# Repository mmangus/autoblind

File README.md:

# Autoblind

## Schematic
[PDF](eda/Autoblind.pdf)

[KiCad file](eda/Autoblind.sch)

## Renders

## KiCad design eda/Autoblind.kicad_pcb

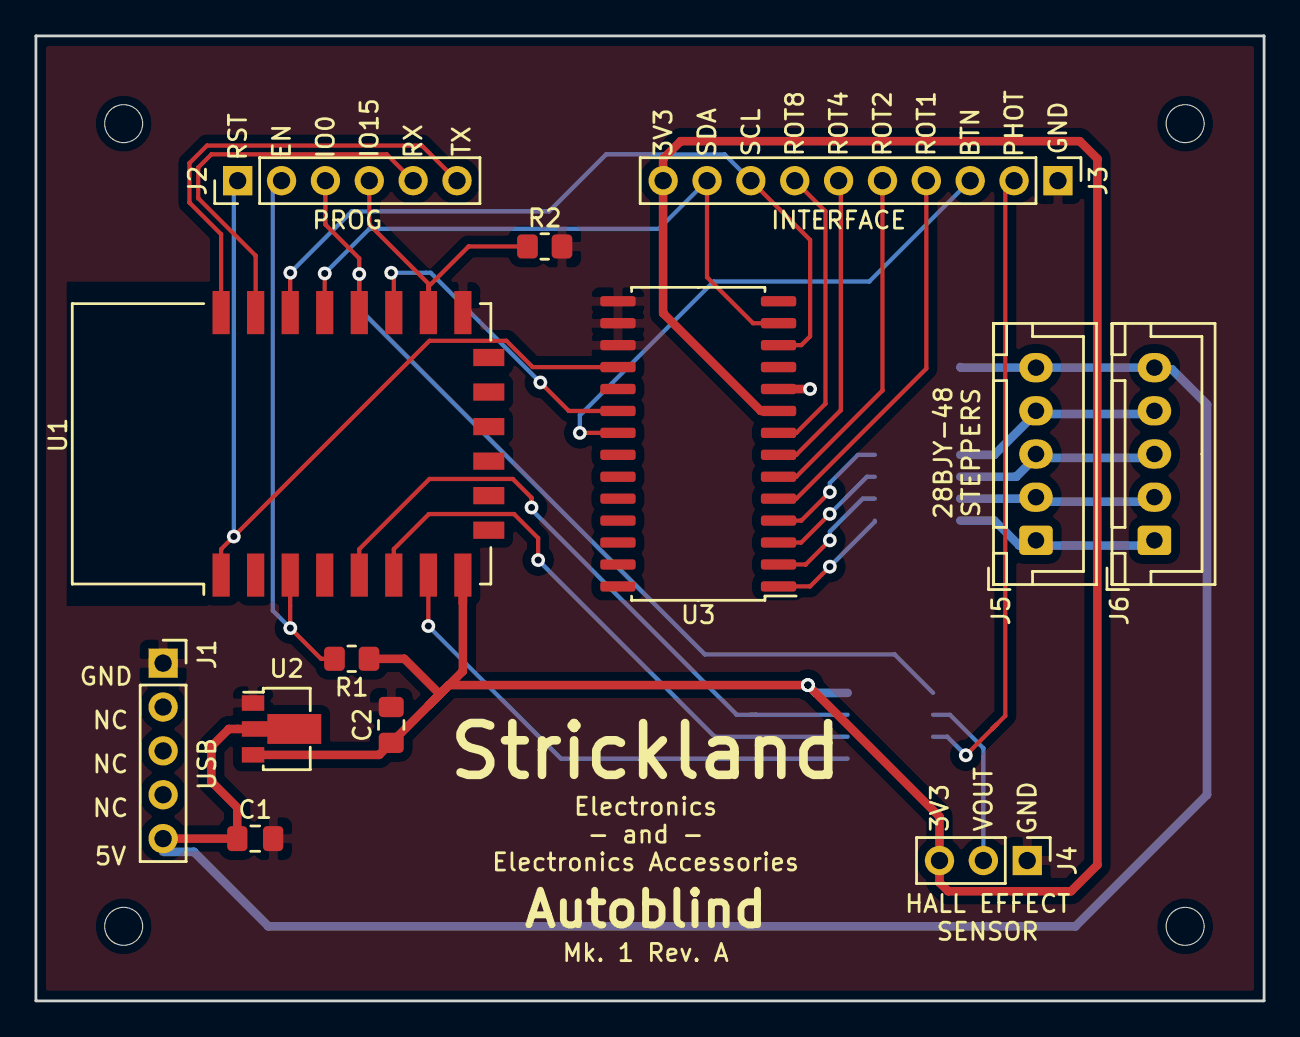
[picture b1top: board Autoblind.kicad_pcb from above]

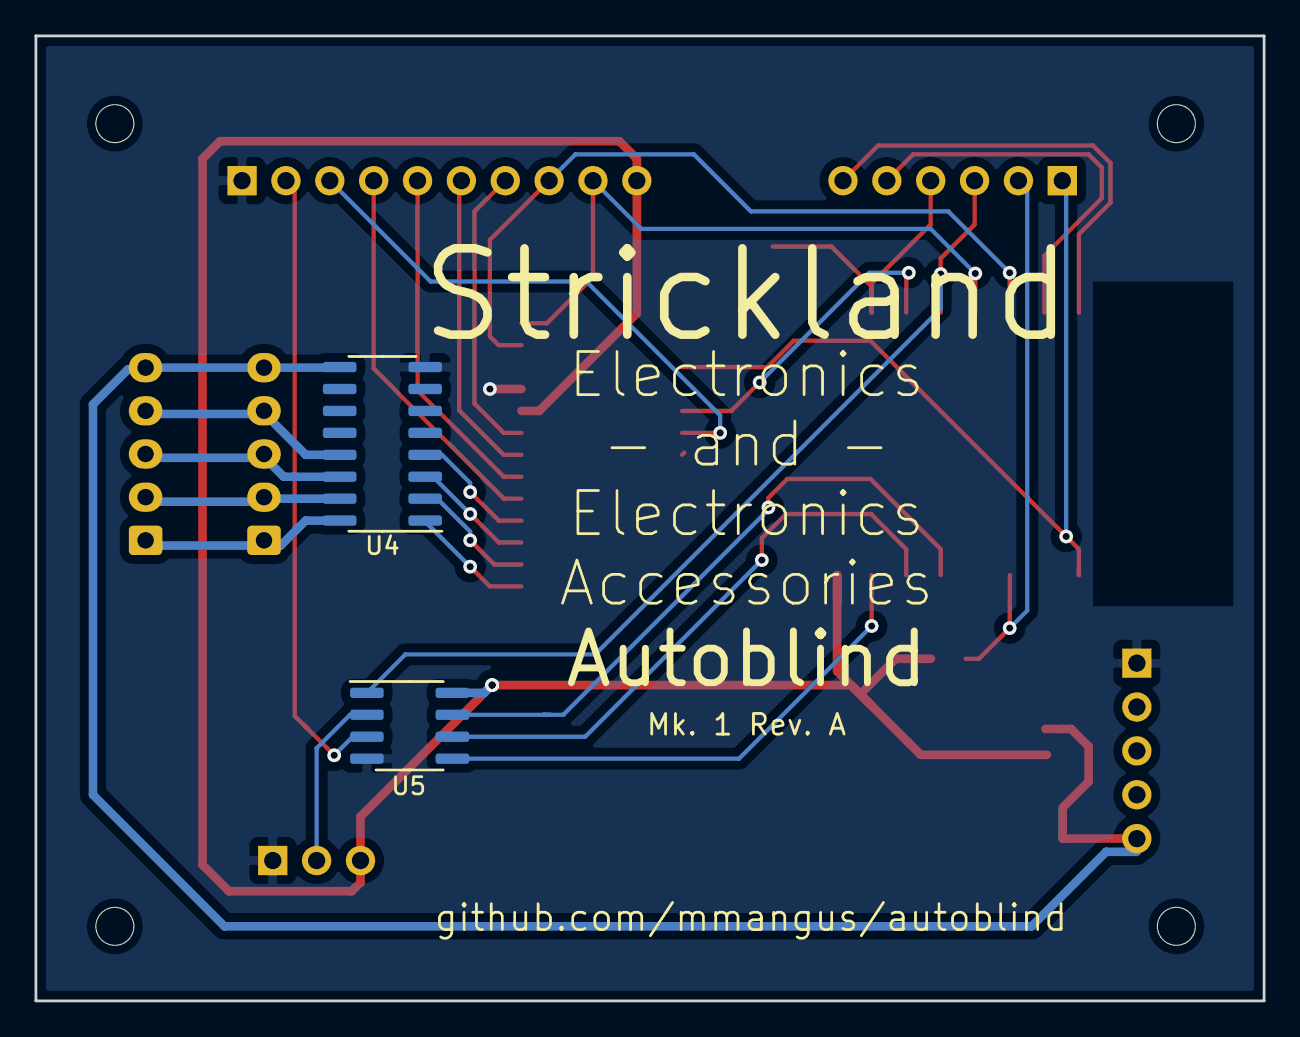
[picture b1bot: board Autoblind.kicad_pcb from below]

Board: 2 copper layers, 71.1 x 55.9 mm, 19 parts (2 on the bottom side), 30 nets.

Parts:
 : MountingHole_2.2mm_M2
 #2,  #3,  #4: MountingHole_2.2mm_M2
C1, C2: 2.2uF; C_0805_2012Metric_Pad1.18x1.45mm_HandSolder
J1: Conn_01x05; PinSocket_1x05_P2.54mm_Vertical
J2: Conn_01x06; PinHeader_1x06_P2.54mm_Vertical
J3: Conn_01x10; PinHeader_1x10_P2.54mm_Vertical
J4: Conn_01x03; PinHeader_1x03_P2.54mm_Vertical
J5, J6: Conn_01x05; JST_XH_B5B-XH-A_1x05_P2.50mm_Vertical
R1: 1K; R_0805_2012Metric_Pad1.20x1.40mm_HandSolder
R2: 470R; R_0805_2012Metric_Pad1.20x1.40mm_HandSolder
U1: ESP-12E
U2: HT7833; SOT-89-3
U3: MCP23017_SO; SOIC-28W_7.5x17.9mm_P1.27mm
U4: ULN2003; SOIC-16_3.9x9.9mm_P1.27mm
U5: MCP3002; SOIC-8_3.9x4.9mm_P1.27mm

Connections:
+3V3: C2.1, J3.10, J4.3, R1.1, U1.8, U2.3, U3.9, U5.8
+5V: C1.1, J1.5, J5.5, J6.5, U2.2, U4.9
/BLUE: J5.1, J6.1, U4.16
/BOOT: J2.4, R2.1, U1.16
/BTN: J3.3, U3.21
/COIL1: U3.1, U4.1
/COIL2: U3.2, U4.2
/COIL3: U3.3, U4.3
/COIL4: U3.4, U4.4
/CS: J2.3, U1.18, U5.1
/EIGHT: J3.7, U3.8
/ENABLE: J2.2, R1.2, U1.3
/FOUR: J3.6, U3.7
/HALL: J4.2, U5.2
/INT: U1.17, U3.20
/MISO: U1.6, U5.6
/MOSI: U1.7, U5.5
/ONE: J3.4, U3.5
/ORANGE: J5.4, J6.4, U4.13
/PHOT: J3.2, U5.3
/PINK: J5.2, J6.2, U4.15
/RESET: J2.1, U1.1, U3.18
/RXD: J2.5, U1.21
/SCL: J3.8, U1.20, U3.12
/SDA: J3.9, U1.19, U3.13
/SPICLK: U1.5, U5.7
/TWO: J3.5, U3.6
/TXD: J2.6, U1.22
/YELLOW: J5.3, J6.3, U4.14
GND: C1.2, C2.2, J1.1, J3.1, J4.1, R2.2, U1.15, U2.1, U3.10, U3.15, U3.16, U3.17, U4.8, U5.4

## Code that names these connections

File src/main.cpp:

#include <Arduino.h>
#include <ESP8266WiFi.h>

#include <ArduinoJson.h>
#include <PubSubClient.h>

#include "autoblind.h"

#define BASE_TOPIC "homeassistant/light/autoblind"
#define AUTODISCOVER_TOPIC BASE_TOPIC "/config"
#define STATE_TOPIC   "homeassistant/autoblind/state"
#define COMMAND_TOPIC "homeassistant/autoblind/set"
#define DEVICE_UUID "c16af742-4724-11eb-b378-0242ac130002"

#define SCALEFACTOR 32  // bri 1-255 -> position 32-8160 (approx 2 full turns of stepper)

#define ORANGE 5
#define YELLOW 13
#define PINK 12
#define BLUE 14

const uint coils[4] = {BLUE, PINK, YELLOW, ORANGE};
uint position = 0;
uint encoderState;
uint lastEncoderState;
int stateChange;

WiFiClient wifiClient;
PubSubClient mqttClient(wifiClient);

void publishAutodiscover() {
  while (!mqttClient.connected()) {
    mqttClient.connect("autoblind");
    delay(100);
  }
  String message;
  StaticJsonDocument<768> jsonMessage;
  jsonMessage["json_attributes_topic"] = BASE_TOPIC;
  jsonMessage["availability_topic"] = STATE_TOPIC;
  jsonMessage["name"] = "autoblind";
  jsonMessage["unique_id"] = DEVICE_UUID;
  jsonMessage["command_topic"] = COMMAND_TOPIC;
  jsonMessage["state_topic"] = STATE_TOPIC;
  jsonMessage["schema"] = "json";
  jsonMessage["brightness"] = true;
  jsonMessage["ct"] = false;
  jsonMessage["xy"] = false;
  JsonObject device = jsonMessage.createNestedObject("device");
  JsonArray identifiers = device.createNestedArray("identifiers");
  identifiers.add(DEVICE_UUID);
  device["name"] = "Autoblind";
  device["model"] = "Autoblind Mk 1";
  device["sw_version"] = "0.1a";
  device["manufacturer"] = "Strickland Electronics and Electronics Accessories";
  serializeJson(jsonMessage, message);

  mqttClient.publish(
    AUTODISCOVER_TOPIC,
    message.c_str(),
    true  // retained
  );
  // delay(1000); some people say we need to wait for pub but idk seems fine
  Serial.println("autodiscovery published");
}

void publishState() {
  String state;
  DynamicJsonDocument stateDoc(256);
  stateDoc["state"] = position > 0 ? "ON" : "OFF";
  // take ceiling
  int brightness = position / SCALEFACTOR + (position % SCALEFACTOR != 0);
  stateDoc["brightness"] = brightness > 0 ? brightness : 1;
  serializeJson(stateDoc, state);
  Serial.println(state);
  // TODO DRY reconnect logic
  while (!mqttClient.connected()) {
    mqttClient.connect("autoblind");
    delay(100);
  }
  mqttClient.publish(
    STATE_TOPIC,
    state.c_str(),
    false  // retained
  );
}

void runStepper(int requestedPosition) {
  uint newPosition;
  if (requestedPosition < 0) {
    // a request for a negative value parks at 0
    newPosition = 0;
  } else {
    newPosition = (uint) requestedPosition;
  }
  Serial.printf("reposition to %d\n", newPosition);
  while (newPosition != position) {
    uint step = position % 8;
    switch(step) {
      case 0:
        digitalWrite(BLUE,   HIGH);
        digitalWrite(PINK,   LOW);
        digitalWrite(YELLOW, LOW);
        digitalWrite(ORANGE, LOW);
        break;
      case 1:
        digitalWrite(BLUE,   HIGH);
        digitalWrite(PINK,   HIGH);
        digitalWrite(YELLOW, LOW);
        digitalWrite(ORANGE, LOW);
        break;
      case 2:
        digitalWrite(BLUE,   LOW);
        digitalWrite(PINK,   HIGH);
        digitalWrite(YELLOW, LOW);
        digitalWrite(ORANGE, LOW);
        break;
      case 3:
        digitalWrite(BLUE,   LOW);
        digitalWrite(PINK,   HIGH);
        digitalWrite(YELLOW, HIGH);
        digitalWrite(ORANGE, LOW);
        break;
      case 4:
        digitalWrite(BLUE,   LOW);
        digitalWrite(PINK,   LOW);
        digitalWrite(YELLOW, HIGH);
        digitalWrite(ORANGE, LOW);
        break;
      case 5:
        digitalWrite(BLUE,   LOW);
        digitalWrite(PINK,   LOW);
        digitalWrite(YELLOW, HIGH);
        digitalWrite(ORANGE, HIGH);
        break;
      case 6:
        digitalWrite(BLUE,   LOW);
        digitalWrite(PINK,   LOW);
        digitalWrite(YELLOW, LOW);
        digitalWrite(ORANGE, HIGH);
        break;
      case 7:
        digitalWrite(BLUE,   HIGH);
        digitalWrite(PINK,   LOW);
        digitalWrite(YELLOW, LOW);
        digitalWrite(ORANGE, HIGH);
        break;
    }
    if (newPosition > position) {
      position++;
    } else {
      position--;
    }
    delay(2);
  }
  for (uint8_t i=0; i < 4; ++i) {
    // all transistors off / coils pulled high
    digitalWrite(coils[i], LOW);
  }
  publishState();
  Serial.printf("moved to position %d\n", position);
}

void mqttCallback(char* topic, byte* payload, uint length) {
  Serial.printf("%s message received\n", topic);
  byte truncatedPayload[length];
  for (uint i = 0; i < length; i++) {
    truncatedPayload[i] = payload[i];
  }
  Serial.println((char*) truncatedPayload);
  DynamicJsonDocument jsonDoc(192);
  DeserializationError jsonError = deserializeJson(jsonDoc, truncatedPayload);
  if (jsonError) {
    Serial.println(jsonError.c_str());
  } else {
    if (strcmp(topic, STATE_TOPIC) == 0) {
      //publishState();  this gets abso spammed... i think i just update it not sub?
    } else if (strcmp(topic, COMMAND_TOPIC) == 0) {
      JsonVariant state = jsonDoc["state"];
      if (!state.isNull() && strcmp(state.as<char*>(), "OFF") == 0) {
        runStepper(0);
        publishState();
      } else {
        JsonVariant brightness = jsonDoc["brightness"];
        // spec is to return to previous position if bri is 0, so no action for us
        if (!brightness.isNull() && brightness.as<int>() > 0) {
          publishState();
          int brightness = jsonDoc["brightness"];
          runStepper(brightness * SCALEFACTOR);
        } else {
          publishState();
        }
      }
    }
  }
}

uint sampleAdc() {
  uint sum = 0;
  uint nSamples = 10;
  delay(50);  // give the cap time to charge all the way up
  for (uint i=0; i < nSamples; i++) {
    sum += analogRead(A0);
  }
  return sum / nSamples;
}

void setup() {
  Serial.begin(9600);
  for (uint8_t i=0; i < 4; ++i) {
    pinMode(coils[i], OUTPUT);
  }
  pinMode(LED_BUILTIN, OUTPUT);
  encoderState = sampleAdc();
  WiFi.begin(SSID, PASSWORD);
  digitalWrite(LED_BUILTIN, LOW);
  while (WiFi.status() != WL_CONNECTED) {
    delay(100);
  }
  digitalWrite(LED_BUILTIN, HIGH);
  mqttClient.setServer(MQTT_SERVER, 1883);
  mqttClient.setCallback(mqttCallback);
  mqttClient.setKeepAlive(120);
  mqttClient.setBufferSize(1024);
}

void loop() {
  lastEncoderState = encoderState;
  encoderState = sampleAdc();
  stateChange = encoderState - lastEncoderState;
  // the rotary encoder makes a voltage divider for the ADC.
  // as the 2 LSB count up, the voltage goes down, and vice-versa:
  // ~750mV, ~550mV, ~350mV, ~0V
  // loops back around every 4 positions.
  // check for reasonable chunks of voltage to account for noise
  if (stateChange >= 500) {
    runStepper(position + 1024);
    encoderState = sampleAdc();
  } else if (stateChange <= -500) {
    runStepper(position - 1024);
    encoderState = sampleAdc();
  } else if (stateChange <= -100) {
    runStepper(position + 1024);
    encoderState = sampleAdc();
  } else if (stateChange >= 100) {
    runStepper(position - 1024);
    encoderState = sampleAdc();
  }
  while (!mqttClient.connected()){
    Serial.println("establishing mqtt connection");
    Serial.printf("state %d\n", mqttClient.state());
    delay(100);
    if (mqttClient.connect("autoblind")) {
      mqttClient.subscribe(STATE_TOPIC);  // status
      mqttClient.subscribe(COMMAND_TOPIC);  //command
      Serial.println("mqtt subscribed");
      publishAutodiscover();
      publishState();
      digitalWrite(LED_BUILTIN, LOW);
      delay(100);
      digitalWrite(LED_BUILTIN, HIGH);
      delay(100);
      digitalWrite(LED_BUILTIN, LOW);
      delay(100);
      digitalWrite(LED_BUILTIN, HIGH);
    }
  }
  mqttClient.loop();
  yield();
}

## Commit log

2020-12-30 Initial commit of local files
